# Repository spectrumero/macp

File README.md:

# ZX Make-a-Chip Pro

Back in the day, there was some software for the Sinclair Spectrum (often
advertised today as "VERY R@RE!!!!11" on eBay) called Make-a-Chip, by
Icognito Software Ltd. It waas a circuit simulator that allowed you to
build simple logic circuits with digital gates (AND, OR, NAND, NOR).

Today, of course, we can go many steps better; we have the FPGA (field
programmable gate array) to play with, and we can realise our own designs,
right up to entire systems on a chip.

2022 is the 40th anniversary of the launch of the Sinclair Spectrum, and
this project is something to celebrate that.

The ZX Make-a-Chip Pro is a board with a Lattice iCE40-HX4K FPGA with
all the level shifting required to connect to a Sinclair Spectrum.
It's designed to work with the open source IceStorm toolchain for
the FPGA used (but will no doubt work just fine with the Lattice
proprietary toolchain, too). Aside from the FPGA, it also has some
static ram (128k x 8, 256k x 8 or 512k x 8), the serial flash to 
hold the FPGA's "gateware" (with room left over for other uses),
a crystal oscillator, interface electronics for the 3.3v to 5v level
translation, and 25 GPIOs for connecting to other things.

## The PCB

A 4-layer PCB. This has been successfully made using PCBWay.

## Major parts

The FPGA is an iCE40-HX4K-TQ144. Unfortunately the HX1K has a sufficiently
different pinout that it won't work. When using arachne-pnr/nextpnr during
place and route, select "8k" as the device and "tq144:4k" as the package.
(In reality, the die in this chip is an HX8K)

Any JEDEC compliant SPI flash chip will work but it **must** support
the page program command. Check the datasheet before you commit to a chip.
While flash that doesn't support paged write will work, you won't be able
to program it with the `iceprog` tool - at least without modifying it to
work with a chip that doesn't support the page program command (and it's
doubtful you will be able to make it work at all with the Lattice
proprietary IDE).

Look for support for 'PP' (command 0x02) in the chip's datasheet.
The chip must also support 64kb block erase.

The gateware requires three 64kb blocks. This gets written to the first
three 64kb blocks. Remaining space in the flash may be used for projects 
(e.g. code), so as long as the flash is bigger than 192kbytes, it's good 
enough.

The RAM is on the 3.3v side of the board, so ensure that the static RAM
works with 3.3v (there are still quite a few 5v static RAM chips that won't
go down to 3.3v). The faster the better. If you only use the static RAM
for the Spectrum side then you can pretty much use any chip you please,
but if you're going to implement a second processor on the FPGA, you
probably want something fairly fast (10ns is available).

The crystal oscillator I use is 25MHz. If you choose a different value,
it's worth checking that it fits in the input limits of the FPGA's
PLL.

The remainder of the devices on the board should be pretty widely availble.

## Special symbols

There are two symbols unique to the project: the ZX edge connector
(designed for through hole mounting) and a schematic symbol for the
74ALVC164245PVG bus translator. The edge connector also has an associated
PCB footprint. See the local-lib directory.

## Programming other parts of the flash with iceprog

The icestorm toolchain's `iceprog` program can do more than just write
the gateware to the flash chip. You can supply it an offset, for example
if you want to store ROM code that will be used later by the FPGA
or copied to RAM, or a FatFS filesystem:

`iceprog -0 0x30000 file.bin`

to write the contents of a file from 0x30000 (the 64k block immediately
following the gateware).

## Recommended programming hardware

The Adafruit FT232H board works well (any similar board with this FTDI
chip should work with `iceprog`). Connect it as follows:

```
D0 -> SCK
D1 -> SDO
D2 -> SDI
D3 (not connected)
D4 -> SS
D5 (not connected)
D6 -> CDONE
D7 -> CRESET
```

You may need to invoke `iceprog` as follows:

`iceprog -d i:0x0403:0x6014 <filename>`

...if it fails to find your FT232H breakout board. (You may need `sudo`
as well).

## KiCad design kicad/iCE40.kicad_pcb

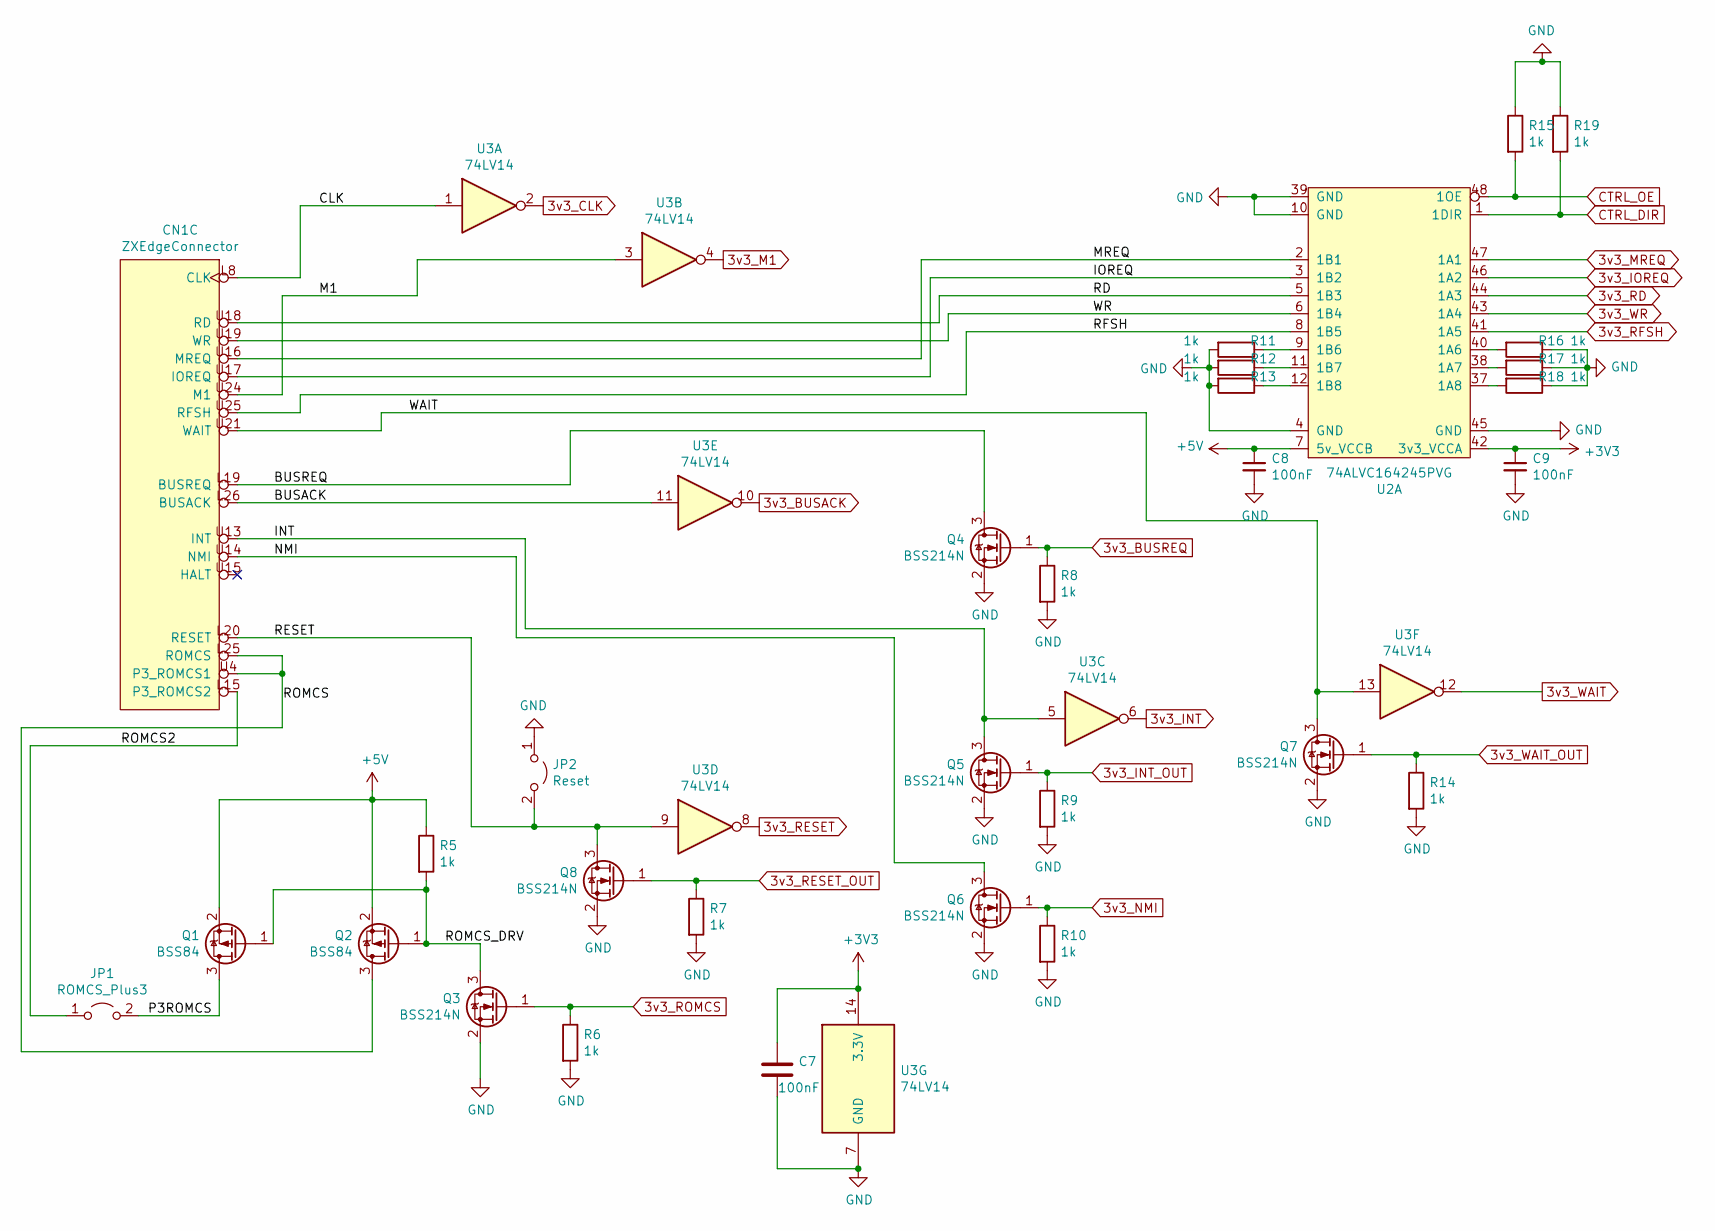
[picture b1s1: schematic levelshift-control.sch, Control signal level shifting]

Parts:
C7, C8, C9: 100nF; C_0603_1608Metric_Pad1.08x0.95mm_HandSolder
CN1: ZXEdgeConnector
JP1: ROMCS_Plus3; PinHeader_1x02_P2.54mm_Vertical
JP2: Reset; PinHeader_1x02_P2.54mm_Vertical
Q1, Q2: BSS84; SOT-23
Q3, Q4, Q5, Q6, Q7, Q8: BSS214N; SOT-23
R5, R6, R7, R8, R9, R10, R11, R12, R13, R14, R15, R16, R17, R18, R19: 1k; R_0603_1608Metric_Pad0.98x0.95mm_HandSolder
U2: 74ALVC164245PVG; SSOP-48_7.5x15.9mm_P0.635mm
U3: 74LV14; SOIC-14_3.9x8.7mm_P1.27mm

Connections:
3v3_BUSACK: U3.10; also elsewhere on the board
3v3_BUSREQ: Q4.1 (G), R8.1; also elsewhere on the board
3v3_CLK: U3.2; also elsewhere on the board
3v3_INT: U3.6; also elsewhere on the board
3v3_INT_OUT: Q5.1 (G), R9.1; also elsewhere on the board
3v3_IOREQ: U2.46 (1A2); also elsewhere on the board
3v3_M1: U3.4; also elsewhere on the board
3v3_MREQ: U2.47 (1A1); also elsewhere on the board
3v3_NMI: Q6.1 (G), R10.1; also elsewhere on the board
3v3_RD: U2.44 (1A3); also elsewhere on the board
3v3_RESET: U3.8; also elsewhere on the board
3v3_RESET_OUT: Q8.1 (G), R7.1; also elsewhere on the board
3v3_RFSH: U2.41 (1A5); also elsewhere on the board
3v3_ROMCS: Q3.1 (G), R6.1; also elsewhere on the board
3v3_WAIT: U3.12; also elsewhere on the board
3v3_WAIT_OUT: Q7.1 (G), R14.1; also elsewhere on the board
3v3_WR: U2.43 (1A4); also elsewhere on the board
+3V3: C7.1, C9.1, U2.42 (3v3_VCCA), U3.14 (3.3V); also elsewhere on the board
+5V: C8.1, Q1.2 (S), Q2.2 (S), R5.1, U2.7 (5v_VCCB); also elsewhere on the board
/levelshift-control/BUSACK: CN1.L26 (BUSACK), U3.11
/levelshift-control/BUSREQ: CN1.L19 (BUSREQ), Q4.3 (D)
/levelshift-control/CLK: CN1.L8 (CLK), U3.1
/levelshift-control/INT: CN1.U13 (INT), Q5.3 (D), U3.5
/levelshift-control/IOREQ: CN1.U17 (IOREQ), U2.3 (1B2)
/levelshift-control/M1: CN1.U24 (M1), U3.3
/levelshift-control/MREQ: CN1.U16 (MREQ), U2.2 (1B1)
/levelshift-control/NMI: CN1.U14 (NMI), Q6.3 (D)
/levelshift-control/P3ROMCS: JP1.2 (B), Q1.3 (D)
/levelshift-control/RD: CN1.U18 (RD), U2.5 (1B3)
/levelshift-control/RESET: CN1.L20 (RESET), JP2.2 (B), Q8.3 (D), U3.9
/levelshift-control/RFSH: CN1.U25 (RFSH), U2.8 (1B5)
/levelshift-control/ROMCS: CN1.L25 (ROMCS), CN1.U4 (P3_ROMCS1), Q2.3 (D)
/levelshift-control/ROMCS2: CN1.L15 (P3_ROMCS2), JP1.1 (A)
/levelshift-control/ROMCS_DRV: Q1.1 (G), Q2.1 (G), Q3.3 (D), R5.2
/levelshift-control/WAIT: CN1.U21 (WAIT), Q7.3 (D), U3.13
/levelshift-control/WR: CN1.U19 (WR), U2.6 (1B4)
CTRL_DIR: R19.2, U2.1 (1DIR); also elsewhere on the board
CTRL_OE: R15.2, U2.48 (1OE); also elsewhere on the board
GND: C7.2, C8.2, C9.2, JP2.1 (A), Q3.2 (S), Q4.2 (S), Q5.2 (S), Q6.2 (S), Q7.2 (S), Q8.2 (S), R6.2, R7.2, R8.2, R9.2, R10.2, R11.2, R12.2, R13.2, R14.2, R15.1, R16.1, R17.1, R18.1, R19.1, U2.4 (GND), U2.10 (GND), U2.39 (GND), U2.45 (GND), U3.7 (GND); also elsewhere on the board
unnamed: R11.1, U2.9 (1B6)
unnamed: R12.1, U2.11 (1B7)
unnamed: R13.1, U2.12 (1B8)
unnamed: R16.2, U2.40 (1A6)
unnamed: R17.2, U2.38 (1A7)
unnamed: R18.2, U2.37 (1A8)

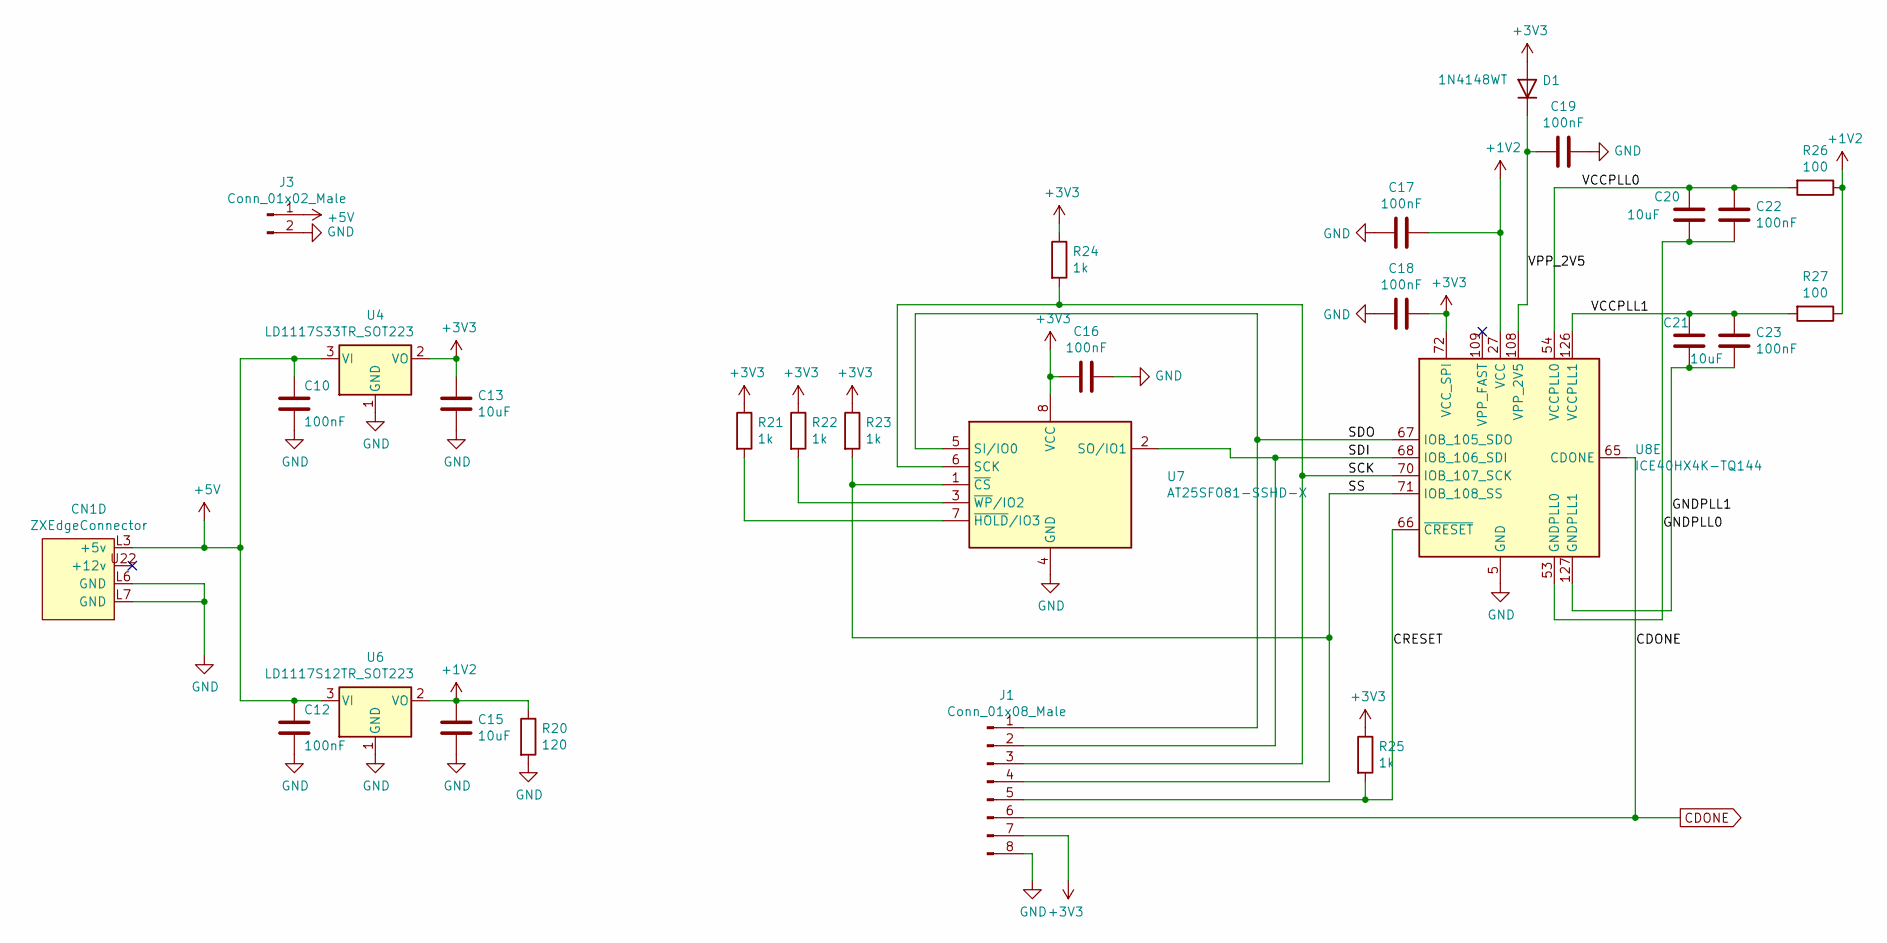
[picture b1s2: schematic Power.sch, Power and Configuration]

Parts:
C10, C12, C16, C17, C18, C19, C22, C23: 100nF; C_0603_1608Metric_Pad1.08x0.95mm_HandSolder
C13, C15, C20, C21: 10uF; C_0805_2012Metric_Pad1.18x1.45mm_HandSolder
CN1: ZXEdgeConnector
D1: 1N4148WT; D_SOD-523
J1: Conn_01x08_Male; PinHeader_1x08_P2.54mm_Vertical
J3: Conn_01x02_Male; PinHeader_1x02_P2.54mm_Vertical
R20: 120; R_0603_1608Metric_Pad0.98x0.95mm_HandSolder
R21, R22, R23, R24, R25: 1k; R_0603_1608Metric_Pad0.98x0.95mm_HandSolder
R26, R27: 100; R_0603_1608Metric_Pad0.98x0.95mm_HandSolder
U4: LD1117S33TR_SOT223; SOT-223-3_TabPin2
U6: LD1117S12TR_SOT223; SOT-223-3_TabPin2
U7: AT25SF081-SSHD-X; SOIC-8_3.9x4.9mm_P1.27mm
U8: ICE40HX4K-TQ144; TQFP-144_20x20mm_P0.5mm

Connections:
+1V2: C15.1, C17.1, R20.1, R26.1, R27.1, U6.2 (VO), U8.27 (VCC), U8.40 (VCC), U8.92 (VCC), U8.111 (VCC)
+3V3: C13.1, C16.2, C18.1, D1.2 (A), J1.7, R21.1, R22.1, R23.1, R24.1, R25.1, U4.2 (VO), U7.8 (VCC), U8.72 (VCC_SPI); also elsewhere on the board
+5V: C10.1, C12.1, CN1.L3 (+5v), J3.1, U4.3 (VI), U6.3 (VI); also elsewhere on the board
/Power And Config/CRESET: J1.5, R25.2, U8.66 (~CRESET)
/Power And Config/GNDPLL0: C20.2, C22.2, U8.53 (GNDPLL0)
/Power And Config/GNDPLL1: C21.2, C23.2, U8.127 (GNDPLL1)
/Power And Config/SCK: J1.3, R24.2, U7.6 (SCK), U8.70 (IOB_107_SCK)
/Power And Config/SDI: J1.2, U7.2 (SO/IO1), U8.68 (IOB_106_SDI)
/Power And Config/SDO: J1.1, U7.5 (SI/IO0), U8.67 (IOB_105_SDO)
/Power And Config/SS: J1.4, R23.2, U7.1 (~CS), U8.71 (IOB_108_SS)
/Power And Config/VCCPLL0: C20.1, C22.1, R26.2, U8.54 (VCCPLL0)
/Power And Config/VCCPLL1: C21.1, C23.1, R27.2, U8.126 (VCCPLL1)
/Power And Config/VPP_2V5: C19.2, D1.1 (K), U8.108 (VPP_2V5)
CDONE: J1.6, U8.65 (CDONE)
GND: C10.2, C12.2, C13.2, C15.2, C16.1, C17.2, C18.2, C19.1, CN1.L6 (GND), CN1.L7 (GND), J1.8, J3.2, R20.2, U4.1 (GND), U6.1 (GND), U7.4 (GND), U8.5 (GND), U8.13 (GND), U8.14 (GND), U8.59 (GND), U8.69 (GND), U8.86 (GND), U8.103 (GND), U8.132 (GND), U8.140 (GND); also elsewhere on the board
unnamed: R21.2, U7.7 (~HOLD~/IO3)
unnamed: R22.2, U7.3 (~WP~/IO2)

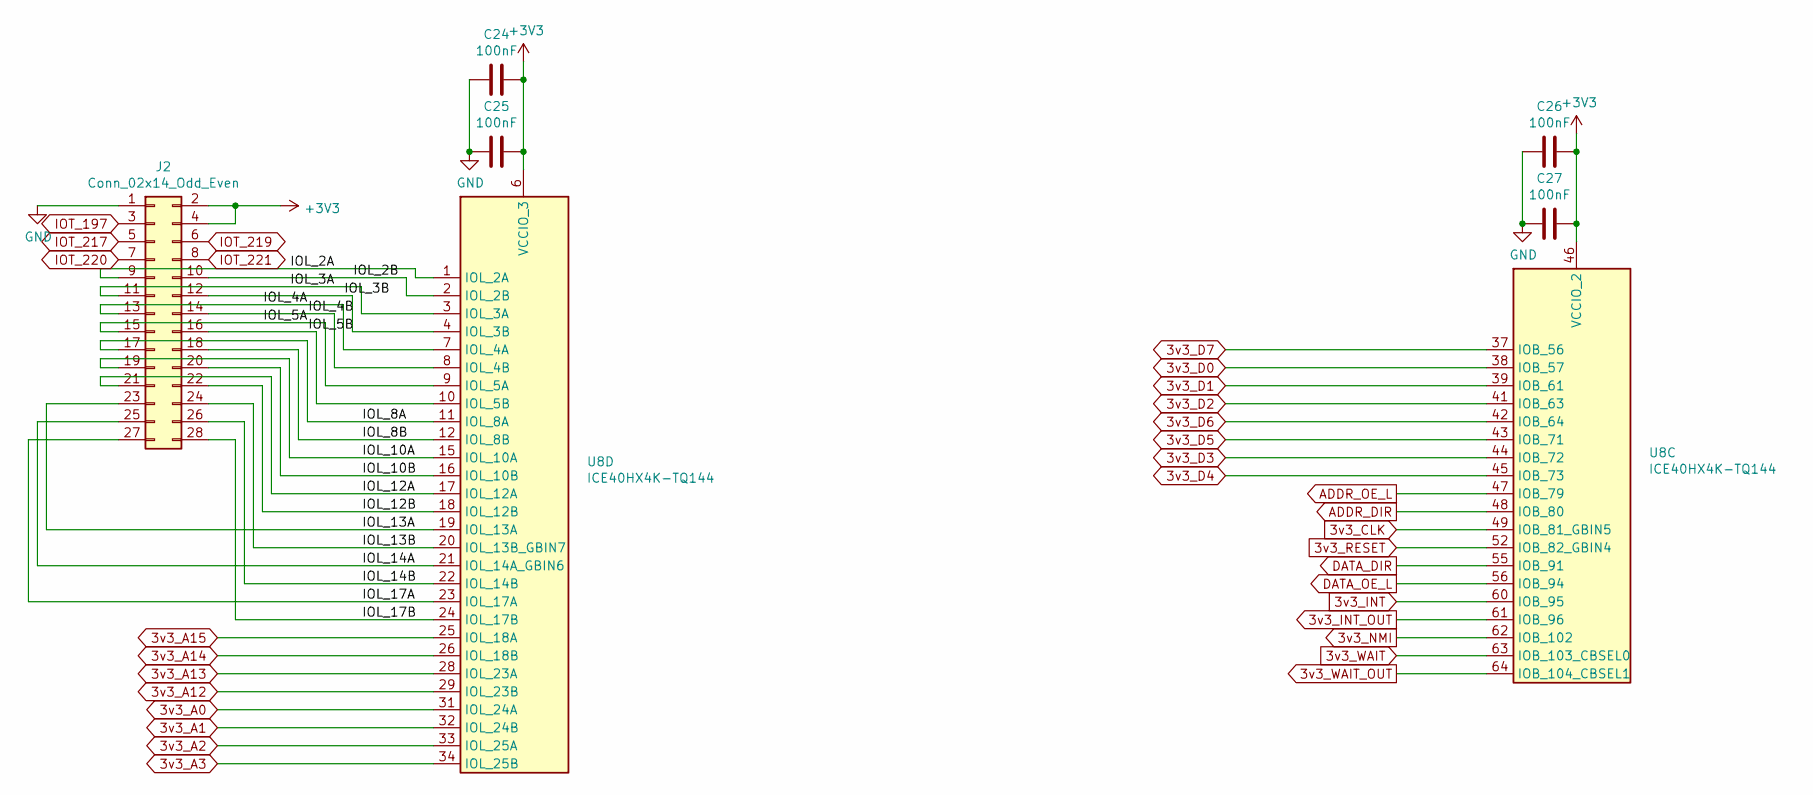
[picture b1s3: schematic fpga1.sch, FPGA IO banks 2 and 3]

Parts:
C24, C25, C26, C27: 100nF; C_0603_1608Metric_Pad1.08x0.95mm_HandSolder
J2: Conn_02x14_Odd_Even; PinHeader_2x14_P2.54mm_Vertical
U8: ICE40HX4K-TQ144; TQFP-144_20x20mm_P0.5mm

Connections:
3v3_A0: U8.31 (IOL_24A); also elsewhere on the board
3v3_A1: U8.32 (IOL_24B); also elsewhere on the board
3v3_A2: U8.33 (IOL_25A); also elsewhere on the board
3v3_A3: U8.34 (IOL_25B); also elsewhere on the board
3v3_A12: U8.29 (IOL_23B); also elsewhere on the board
3v3_A13: U8.28 (IOL_23A); also elsewhere on the board
3v3_A14: U8.26 (IOL_18B); also elsewhere on the board
3v3_A15: U8.25 (IOL_18A); also elsewhere on the board
3v3_CLK: U8.49 (IOB_81_GBIN5); also elsewhere on the board
3v3_D0: U8.38 (IOB_57); also elsewhere on the board
3v3_D1: U8.39 (IOB_61); also elsewhere on the board
3v3_D2: U8.41 (IOB_63); also elsewhere on the board
3v3_D3: U8.44 (IOB_72); also elsewhere on the board
3v3_D4: U8.45 (IOB_73); also elsewhere on the board
3v3_D5: U8.43 (IOB_71); also elsewhere on the board
3v3_D6: U8.42 (IOB_64); also elsewhere on the board
3v3_D7: U8.37 (IOB_56); also elsewhere on the board
3v3_INT: U8.60 (IOB_95); also elsewhere on the board
3v3_INT_OUT: U8.61 (IOB_96); also elsewhere on the board
3v3_NMI: U8.62 (IOB_102); also elsewhere on the board
3v3_RESET: U8.52 (IOB_82_GBIN4); also elsewhere on the board
3v3_WAIT: U8.63 (IOB_103_CBSEL0); also elsewhere on the board
3v3_WAIT_OUT: U8.64 (IOB_104_CBSEL1); also elsewhere on the board
+3V3: C24.1, C25.2, C26.1, C27.2, J2.2, J2.4, U8.6 (VCCIO_3), U8.30 (VCCIO_3), U8.46 (VCCIO_2), U8.57 (VCCIO_2); also elsewhere on the board
/FPGA1/IOL_2A: J2.9, U8.1 (IOL_2A)
/FPGA1/IOL_2B: J2.10, U8.2 (IOL_2B)
/FPGA1/IOL_3A: J2.11, U8.3 (IOL_3A)
/FPGA1/IOL_3B: J2.12, U8.4 (IOL_3B)
/FPGA1/IOL_4A: J2.13, U8.7 (IOL_4A)
/FPGA1/IOL_4B: J2.14, U8.8 (IOL_4B)
/FPGA1/IOL_5A: J2.15, U8.9 (IOL_5A)
/FPGA1/IOL_5B: J2.16, U8.10 (IOL_5B)
/FPGA1/IOL_8A: J2.17, U8.11 (IOL_8A)
/FPGA1/IOL_8B: J2.18, U8.12 (IOL_8B)
/FPGA1/IOL_10A: J2.19, U8.15 (IOL_10A)
/FPGA1/IOL_10B: J2.20, U8.16 (IOL_10B)
/FPGA1/IOL_12A: J2.21, U8.17 (IOL_12A)
/FPGA1/IOL_12B: J2.22, U8.18 (IOL_12B)
/FPGA1/IOL_13A: J2.23, U8.19 (IOL_13A)
/FPGA1/IOL_13B: J2.24, U8.20 (IOL_13B_GBIN7)
/FPGA1/IOL_14A: J2.25, U8.21 (IOL_14A_GBIN6)
/FPGA1/IOL_14B: J2.26, U8.22 (IOL_14B)
/FPGA1/IOL_17A: J2.27, U8.23 (IOL_17A)
/FPGA1/IOL_17B: J2.28, U8.24 (IOL_17B)
ADDR_DIR: U8.48 (IOB_80); also elsewhere on the board
ADDR_OE_L: U8.47 (IOB_79); also elsewhere on the board
DATA_DIR: U8.55 (IOB_91); also elsewhere on the board
DATA_OE_L: U8.56 (IOB_94); also elsewhere on the board
GND: C24.2, C25.1, C26.2, C27.1, J2.1; also elsewhere on the board
IOT_197: J2.3; also elsewhere on the board
IOT_217: J2.5; also elsewhere on the board
IOT_219: J2.6; also elsewhere on the board
IOT_220: J2.7; also elsewhere on the board
IOT_221: J2.8; also elsewhere on the board

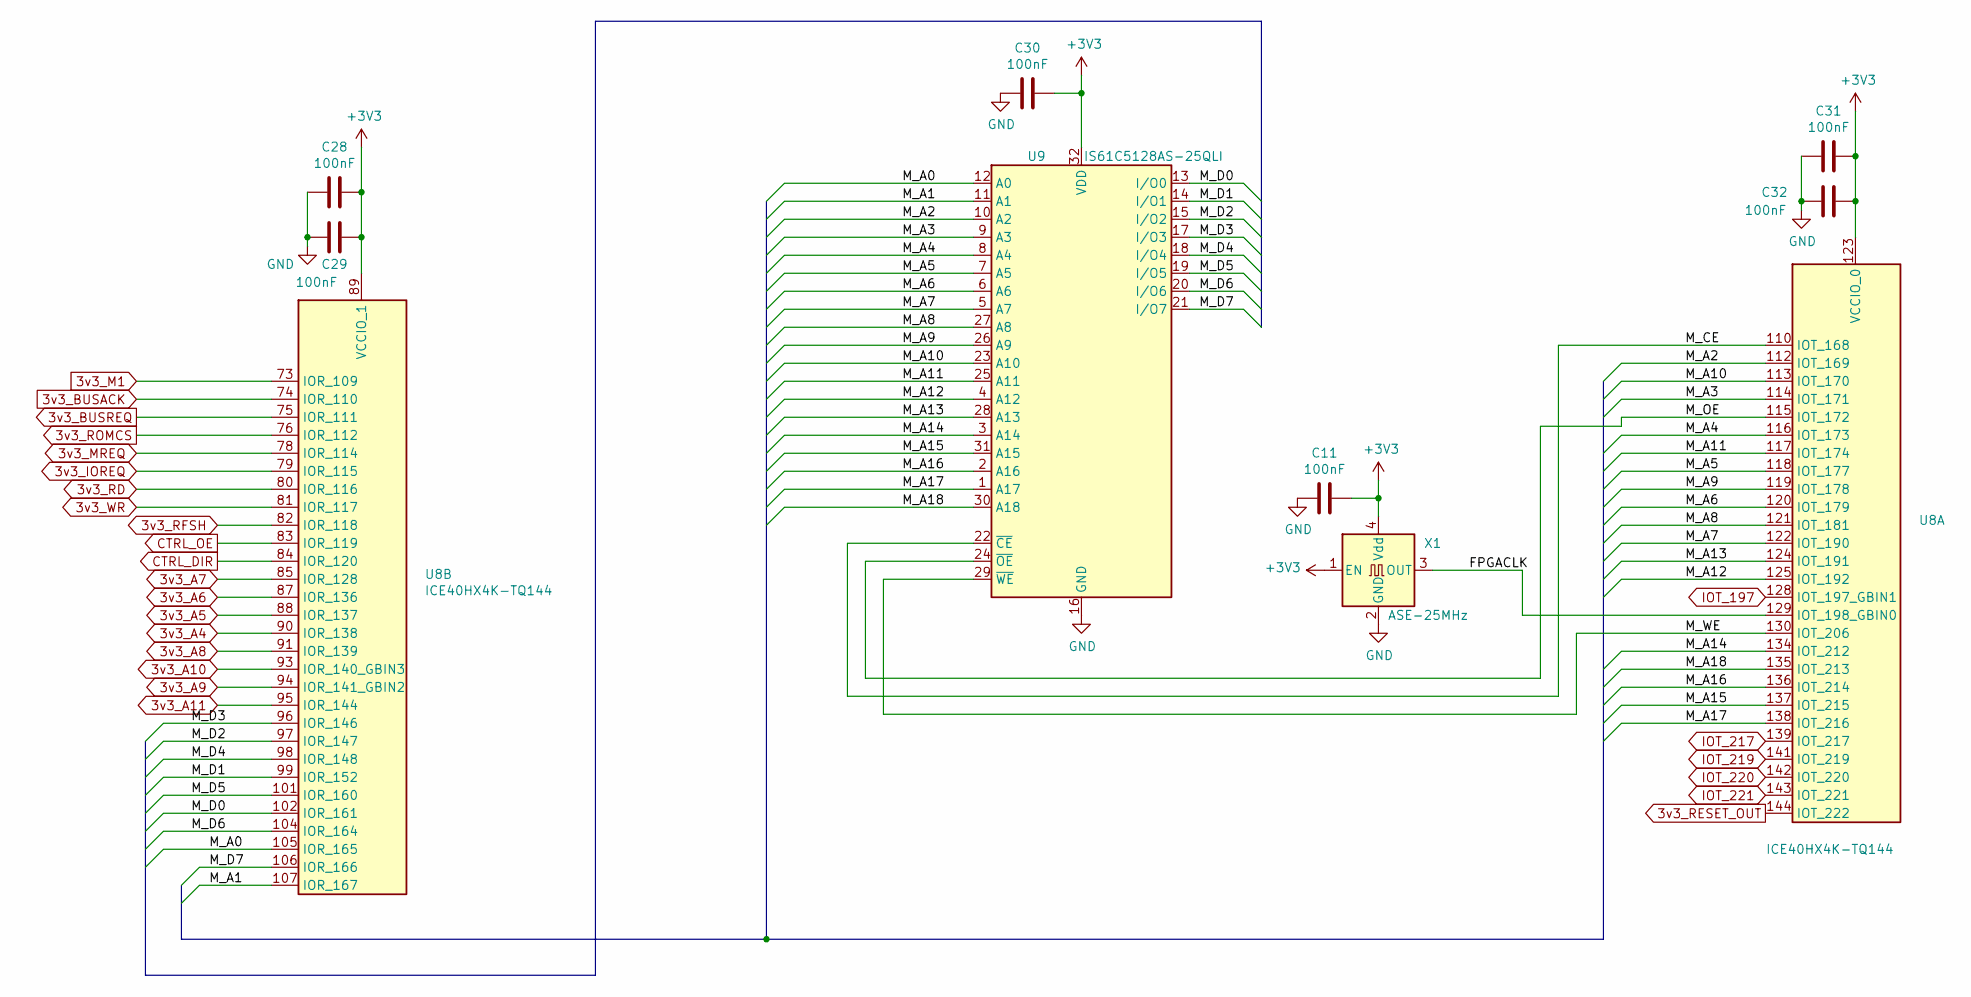
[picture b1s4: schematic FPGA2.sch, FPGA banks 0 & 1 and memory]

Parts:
C11, C28, C29, C30, C31, C32: 100nF; C_0603_1608Metric_Pad1.08x0.95mm_HandSolder
U8: ICE40HX4K-TQ144; TQFP-144_20x20mm_P0.5mm
U9: IS61C5128AS-25QLI; SSOP-32_11.305x20.495mm_P1.27mm
X1: ASE-25MHz; Oscillator_SMD_Abracon_ASE-4Pin_3.2x2.5mm

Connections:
3v3_A4: U8.90 (IOR_138); also elsewhere on the board
3v3_A5: U8.88 (IOR_137); also elsewhere on the board
3v3_A6: U8.87 (IOR_136); also elsewhere on the board
3v3_A7: U8.85 (IOR_128); also elsewhere on the board
3v3_A8: U8.91 (IOR_139); also elsewhere on the board
3v3_A9: U8.94 (IOR_141_GBIN2); also elsewhere on the board
3v3_A10: U8.93 (IOR_140_GBIN3); also elsewhere on the board
3v3_A11: U8.95 (IOR_144); also elsewhere on the board
3v3_BUSACK: U8.74 (IOR_110); also elsewhere on the board
3v3_BUSREQ: U8.75 (IOR_111); also elsewhere on the board
3v3_IOREQ: U8.79 (IOR_115); also elsewhere on the board
3v3_M1: U8.73 (IOR_109); also elsewhere on the board
3v3_MREQ: U8.78 (IOR_114); also elsewhere on the board
3v3_RD: U8.80 (IOR_116); also elsewhere on the board
3v3_RESET_OUT: U8.144 (IOT_222); also elsewhere on the board
3v3_RFSH: U8.82 (IOR_118); also elsewhere on the board
3v3_ROMCS: U8.76 (IOR_112); also elsewhere on the board
3v3_WR: U8.81 (IOR_117); also elsewhere on the board
+3V3: C11.1, C28.1, C29.1, C30.1, C31.1, C32.1, U8.89 (VCCIO_1), U8.100 (VCCIO_1), U8.123 (VCCIO_0), U8.131 (VCCIO_0), U9.32 (VDD), X1.1 (EN), X1.4 (Vdd); also elsewhere on the board
/FPGA2/FPGACLK: U8.129 (IOT_198_GBIN0), X1.3 (OUT)
/FPGA2/M_A0: U8.105 (IOR_165), U9.12 (A0)
/FPGA2/M_A1: U8.107 (IOR_167), U9.11 (A1)
/FPGA2/M_A2: U8.112 (IOT_169), U9.10 (A2)
/FPGA2/M_A3: U8.114 (IOT_171), U9.9 (A3)
/FPGA2/M_A4: U8.116 (IOT_173), U9.8 (A4)
/FPGA2/M_A5: U8.118 (IOT_177), U9.7 (A5)
/FPGA2/M_A6: U8.120 (IOT_179), U9.6 (A6)
/FPGA2/M_A7: U8.122 (IOT_190), U9.5 (A7)
/FPGA2/M_A8: U8.121 (IOT_181), U9.27 (A8)
/FPGA2/M_A9: U8.119 (IOT_178), U9.26 (A9)
/FPGA2/M_A10: U8.113 (IOT_170), U9.23 (A10)
/FPGA2/M_A11: U8.117 (IOT_174), U9.25 (A11)
/FPGA2/M_A12: U8.125 (IOT_192), U9.4 (A12)
/FPGA2/M_A13: U8.124 (IOT_191), U9.28 (A13)
/FPGA2/M_A14: U8.134 (IOT_212), U9.3 (A14)
/FPGA2/M_A15: U8.137 (IOT_215), U9.31 (A15)
/FPGA2/M_A16: U8.136 (IOT_214), U9.2 (A16)
/FPGA2/M_A17: U8.138 (IOT_216), U9.1 (A17)
/FPGA2/M_A18: U8.135 (IOT_213), U9.30 (A18)
/FPGA2/M_CE: U8.110 (IOT_168), U9.22 (~CE)
/FPGA2/M_D0: U8.102 (IOR_161), U9.13 (I/O0)
/FPGA2/M_D1: U8.99 (IOR_152), U9.14 (I/O1)
/FPGA2/M_D2: U8.97 (IOR_147), U9.15 (I/O2)
/FPGA2/M_D3: U8.96 (IOR_146), U9.17 (I/O3)
/FPGA2/M_D4: U8.98 (IOR_148), U9.18 (I/O4)
/FPGA2/M_D5: U8.101 (IOR_160), U9.19 (I/O5)
/FPGA2/M_D6: U8.104 (IOR_164), U9.20 (I/O6)
/FPGA2/M_D7: U8.106 (IOR_166), U9.21 (I/O7)
/FPGA2/M_OE: U8.115 (IOT_172), U9.24 (~OE)
/FPGA2/M_WE: U8.130 (IOT_206), U9.29 (~WE)
CTRL_DIR: U8.84 (IOR_120); also elsewhere on the board
CTRL_OE: U8.83 (IOR_119); also elsewhere on the board
GND: C11.2, C28.2, C29.2, C30.2, C31.2, C32.2, U9.16 (GND), X1.2 (GND); also elsewhere on the board
IOT_197: U8.128 (IOT_197_GBIN1); also elsewhere on the board
IOT_217: U8.139 (IOT_217); also elsewhere on the board
IOT_219: U8.141 (IOT_219); also elsewhere on the board
IOT_220: U8.142 (IOT_220); also elsewhere on the board
IOT_221: U8.143 (IOT_221); also elsewhere on the board

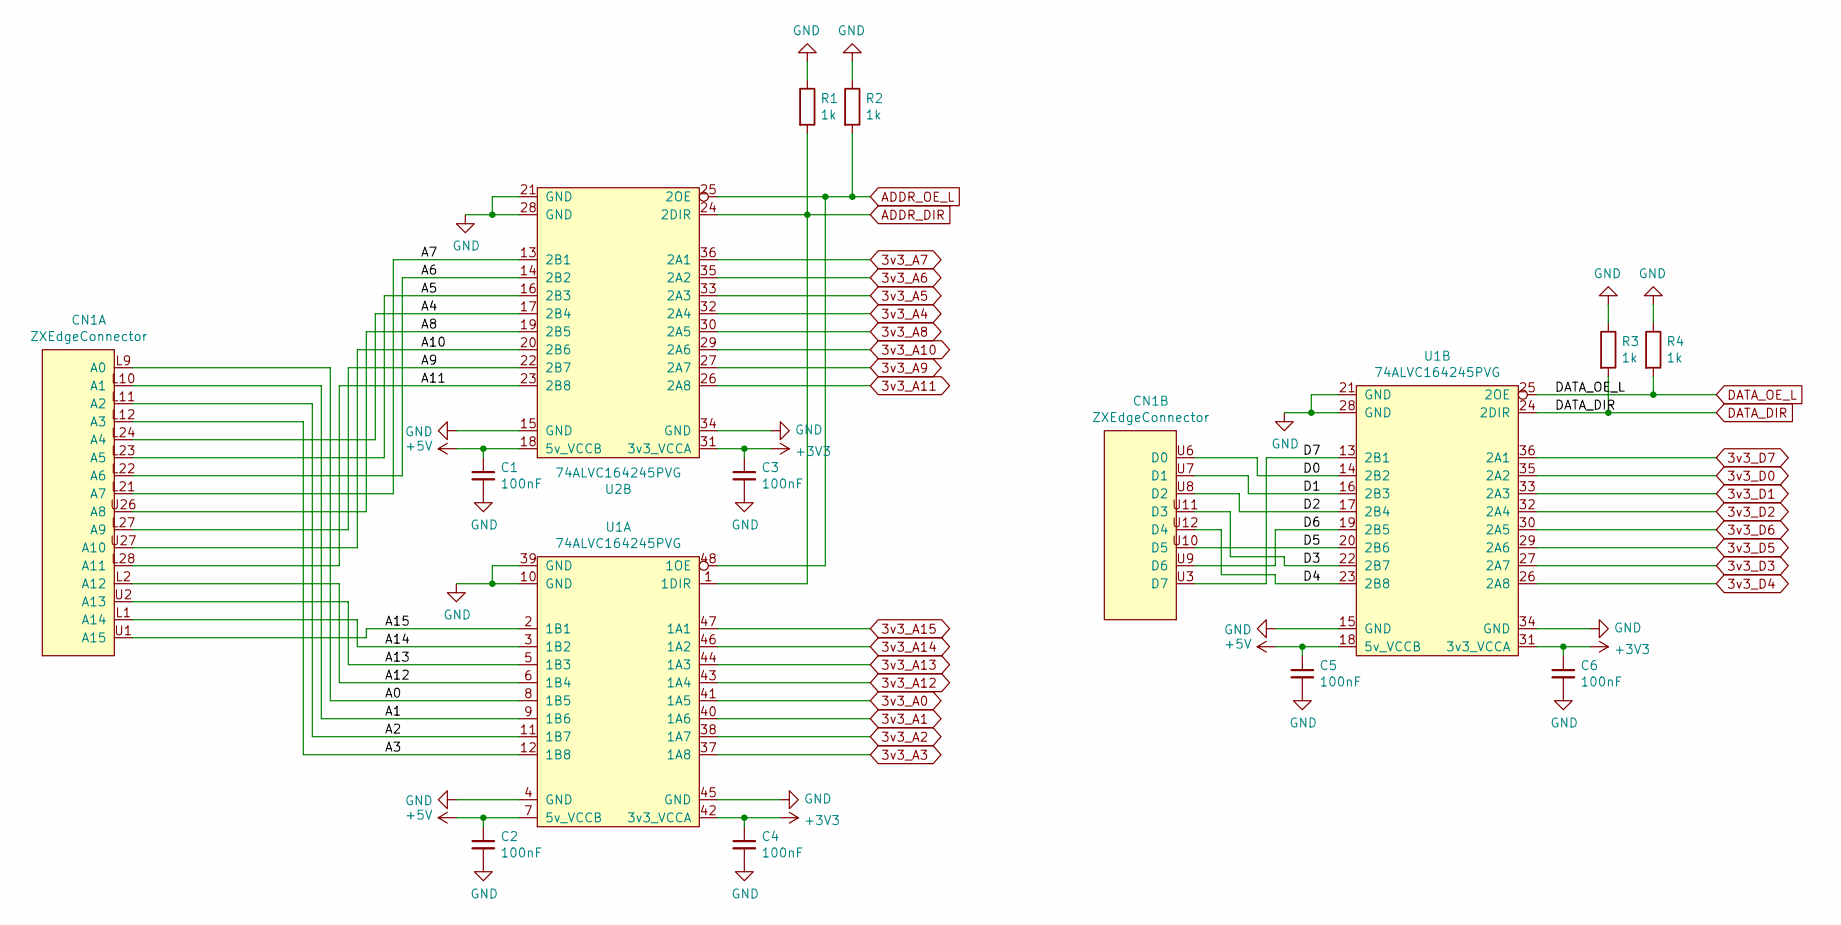
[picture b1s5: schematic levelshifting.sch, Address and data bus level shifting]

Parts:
C1, C2, C3, C4, C5, C6: 100nF; C_0603_1608Metric_Pad1.08x0.95mm_HandSolder
CN1: ZXEdgeConnector
R1, R2, R3, R4: 1k; R_0603_1608Metric_Pad0.98x0.95mm_HandSolder
U1, U2: 74ALVC164245PVG; SSOP-48_7.5x15.9mm_P0.635mm

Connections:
3v3_A0: U1.41 (1A5); also elsewhere on the board
3v3_A1: U1.40 (1A6); also elsewhere on the board
3v3_A2: U1.38 (1A7); also elsewhere on the board
3v3_A3: U1.37 (1A8); also elsewhere on the board
3v3_A4: U2.32 (2A4); also elsewhere on the board
3v3_A5: U2.33 (2A3); also elsewhere on the board
3v3_A6: U2.35 (2A2); also elsewhere on the board
3v3_A7: U2.36 (2A1); also elsewhere on the board
3v3_A8: U2.30 (2A5); also elsewhere on the board
3v3_A9: U2.27 (2A7); also elsewhere on the board
3v3_A10: U2.29 (2A6); also elsewhere on the board
3v3_A11: U2.26 (2A8); also elsewhere on the board
3v3_A12: U1.43 (1A4); also elsewhere on the board
3v3_A13: U1.44 (1A3); also elsewhere on the board
3v3_A14: U1.46 (1A2); also elsewhere on the board
3v3_A15: U1.47 (1A1); also elsewhere on the board
3v3_D0: U1.35 (2A2); also elsewhere on the board
3v3_D1: U1.33 (2A3); also elsewhere on the board
3v3_D2: U1.32 (2A4); also elsewhere on the board
3v3_D3: U1.27 (2A7); also elsewhere on the board
3v3_D4: U1.26 (2A8); also elsewhere on the board
3v3_D5: U1.29 (2A6); also elsewhere on the board
3v3_D6: U1.30 (2A5); also elsewhere on the board
3v3_D7: U1.36 (2A1); also elsewhere on the board
+3V3: C3.1, C4.1, C6.1, U1.31 (3v3_VCCA), U1.42 (3v3_VCCA), U2.31 (3v3_VCCA); also elsewhere on the board
+5V: C1.1, C2.1, C5.1, U1.7 (5v_VCCB), U1.18 (5v_VCCB), U2.18 (5v_VCCB); also elsewhere on the board
/levelshifting/A0: CN1.L9 (A0), U1.8 (1B5)
/levelshifting/A1: CN1.L10 (A1), U1.9 (1B6)
/levelshifting/A2: CN1.L11 (A2), U1.11 (1B7)
/levelshifting/A3: CN1.L12 (A3), U1.12 (1B8)
/levelshifting/A4: CN1.L24 (A4), U2.17 (2B4)
/levelshifting/A5: CN1.L23 (A5), U2.16 (2B3)
/levelshifting/A6: CN1.L22 (A6), U2.14 (2B2)
/levelshifting/A7: CN1.L21 (A7), U2.13 (2B1)
/levelshifting/A8: CN1.U26 (A8), U2.19 (2B5)
/levelshifting/A9: CN1.L27 (A9), U2.22 (2B7)
/levelshifting/A10: CN1.U27 (A10), U2.20 (2B6)
/levelshifting/A11: CN1.L28 (A11), U2.23 (2B8)
/levelshifting/A12: CN1.L2 (A12), U1.6 (1B4)
/levelshifting/A13: CN1.U2 (A13), U1.5 (1B3)
/levelshifting/A14: CN1.L1 (A14), U1.3 (1B2)
/levelshifting/A15: CN1.U1 (A15), U1.2 (1B1)
/levelshifting/D0: CN1.U6 (D0), U1.14 (2B2)
/levelshifting/D1: CN1.U7 (D1), U1.16 (2B3)
/levelshifting/D2: CN1.U8 (D2), U1.17 (2B4)
/levelshifting/D3: CN1.U11 (D3), U1.22 (2B7)
/levelshifting/D4: CN1.U12 (D4), U1.23 (2B8)
/levelshifting/D5: CN1.U10 (D5), U1.20 (2B6)
/levelshifting/D6: CN1.U9 (D6), U1.19 (2B5)
/levelshifting/D7: CN1.U3 (D7), U1.13 (2B1)
ADDR_DIR: R1.2, U1.1 (1DIR), U2.24 (2DIR); also elsewhere on the board
ADDR_OE_L: R2.2, U1.48 (1OE), U2.25 (2OE); also elsewhere on the board
DATA_DIR: R3.2, U1.24 (2DIR); also elsewhere on the board
DATA_OE_L: R4.2, U1.25 (2OE); also elsewhere on the board
GND: C1.2, C2.2, C3.2, C4.2, C5.2, C6.2, R1.1, R2.1, R3.1, R4.1, U1.4 (GND), U1.10 (GND), U1.15 (GND), U1.21 (GND), U1.28 (GND), U1.34 (GND), U1.39 (GND), U1.45 (GND), U2.15 (GND), U2.21 (GND), U2.28 (GND), U2.34 (GND); also elsewhere on the board

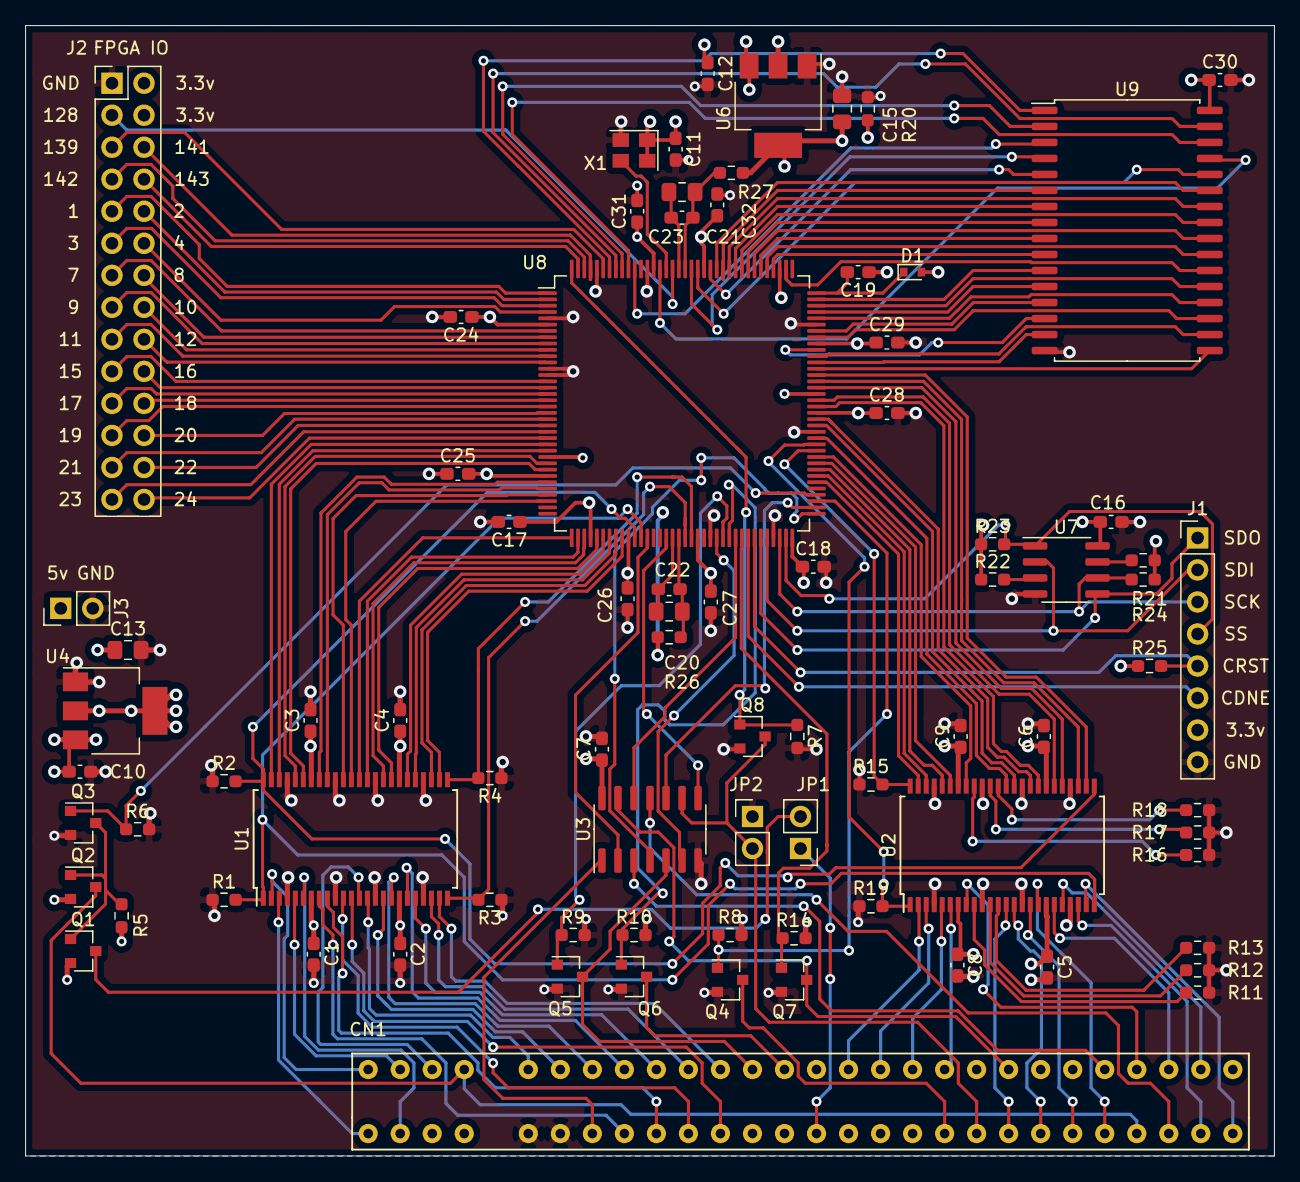
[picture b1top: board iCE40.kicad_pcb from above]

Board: 4 copper layers, 99.1 x 89.7 mm, 82 parts (0 on the bottom side), 167 nets.

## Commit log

2022-07-19 Hardware files
2022-07-19 readme file
2022-07-19 add .pro file
2022-07-19 readme formatting fixes
